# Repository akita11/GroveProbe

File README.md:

# GroveProbe

2本のGroveケーブルを接続して延長し、その途中の信号線をピンソケットに引き出します。Groveケーブルの延長と、信号の観測に使えます。

## Author

Junichi Akita (akita@ifdl.jp, @akita11)

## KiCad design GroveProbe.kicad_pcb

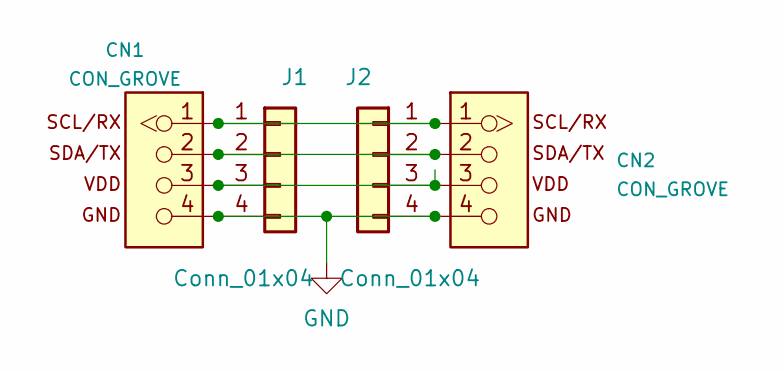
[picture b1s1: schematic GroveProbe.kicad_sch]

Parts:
CN1, CN2: CON_GROVE; CON_GROVE_H
J1, J2: Conn_01x04; PinSocket_1x04_P2.54mm_Vertical

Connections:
GND: CN1.4, CN2.4, J1.4, J2.4
unnamed: CN1.1, CN2.1, J1.1, J2.1
unnamed: CN1.2, CN2.2, J1.2, J2.2
unnamed: CN1.3, CN2.3, J1.3, J2.3

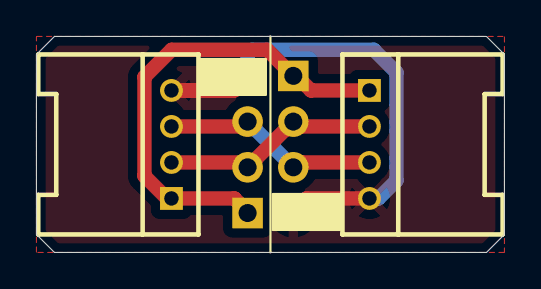
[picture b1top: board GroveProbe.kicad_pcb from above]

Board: 2 copper layers, 26.0 x 12.0 mm, 4 parts (0 on the bottom side), 4 nets.
